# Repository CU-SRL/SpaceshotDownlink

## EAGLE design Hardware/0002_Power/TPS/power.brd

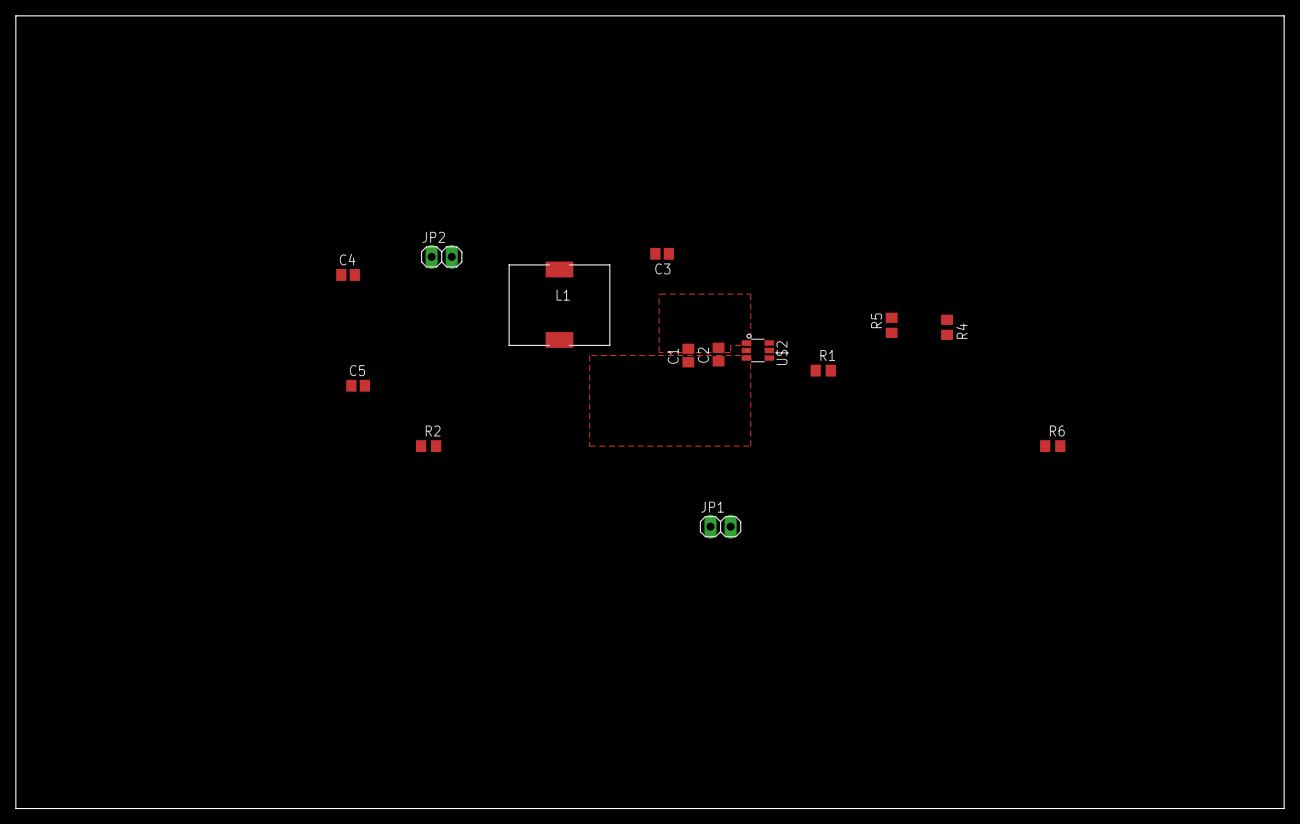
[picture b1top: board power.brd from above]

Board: 2 copper layers, 160.0 x 100.0 mm, 14 parts (0 on the bottom side), 8 nets, no tracks yet.

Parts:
C1: 10uF; C2012
C2, C3: 0.1uF; C2012
C4, C5: 22uF; C2012
JP1, JP2: 1X02
L1: 7447714100
R1: 511k; R0805
R2: 105k; R0805
R4: 100k; R0805
R5: 22.1k; R0805
R6: 2k; R0805
U$2: TPS54308; SOT-23-6

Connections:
+12V: C1.1, C2.1, JP1.2, R1.2, U$2.3
GND: C1.2, C2.2, C4.2, C5.2, JP1.1, JP2.2, R2.1, R5.1, U$2.1
unnamed: R1.1, R2.2, U$2.5
unnamed: C3.1, U$2.6
unnamed: C3.2, L1.P$1, U$2.2
unnamed: C4.1, C5.1, JP2.1, L1.P$2
unnamed: R4.2, R6.1
unnamed: R4.1, R5.2, U$2.4

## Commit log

2020-01-24 add signal budget
2020-01-24 add transmitter project
2020-01-24 add .gitignore
2020-01-24 add transmitter-cache.lib
2020-02-01 Add updated signal budget and parts list
2020-02-03 synth pin allocations
2020-02-03 add 0001_Transmitter.lib
2020-02-03 add lots of footprints
2020-02-05 updated schematic 1
2020-02-08 updated schematic
2020-02-10 Added software folder with minimal files
2020-02-10 fix 0001_Transmitter directories
2020-02-10 add xo
2020-02-10 add gitignore for ods lock files
2020-02-10 Working on lmx library, making macros
2020-02-11 Finished minor abstracted macros for future use
2020-02-11 Added minor functions for lmx2572
2020-02-11 Added files to arduino ide
2020-02-12 fixed a bunch of the library stuff (hopefully)
2020-02-12 Added some additional functions
2020-02-13 fixed some more stuff, needs to be double checked & prettified
2020-02-14 tcxo and vcxo
2020-02-18 verified some cap values, moved some stuff around to make it look better
2020-02-18 Revamped the entire library
2020-02-29 eagle
2020-02-29 add spaceshot_custom lib
2020-03-01 TPS54308 symbol & footprint
2020-03-01 created device for TPS
2020-03-01 added TPS to main lib
2020-03-01 add footprint & device for lmx - need to connect
2020-03-01 add eagle to gitignore
2020-03-01 Code compiles, needed to add default values and check over an oscilloscope
2020-03-01 Updated with default start values for structs
2020-03-04 added inductor symbol & fp for TPS
2020-03-04 updated schematic for power evalutation board
2020-03-04 added inductor symbol & fp to main lib
2020-03-04 power evaluation board
2020-03-06 RF power updated schematic & board (in progress)
